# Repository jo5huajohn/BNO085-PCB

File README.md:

# BNO085 Breakout Board

Built using KiCad.

## PCB

## Schematic

## 3D Renders

Front Render

Back Render

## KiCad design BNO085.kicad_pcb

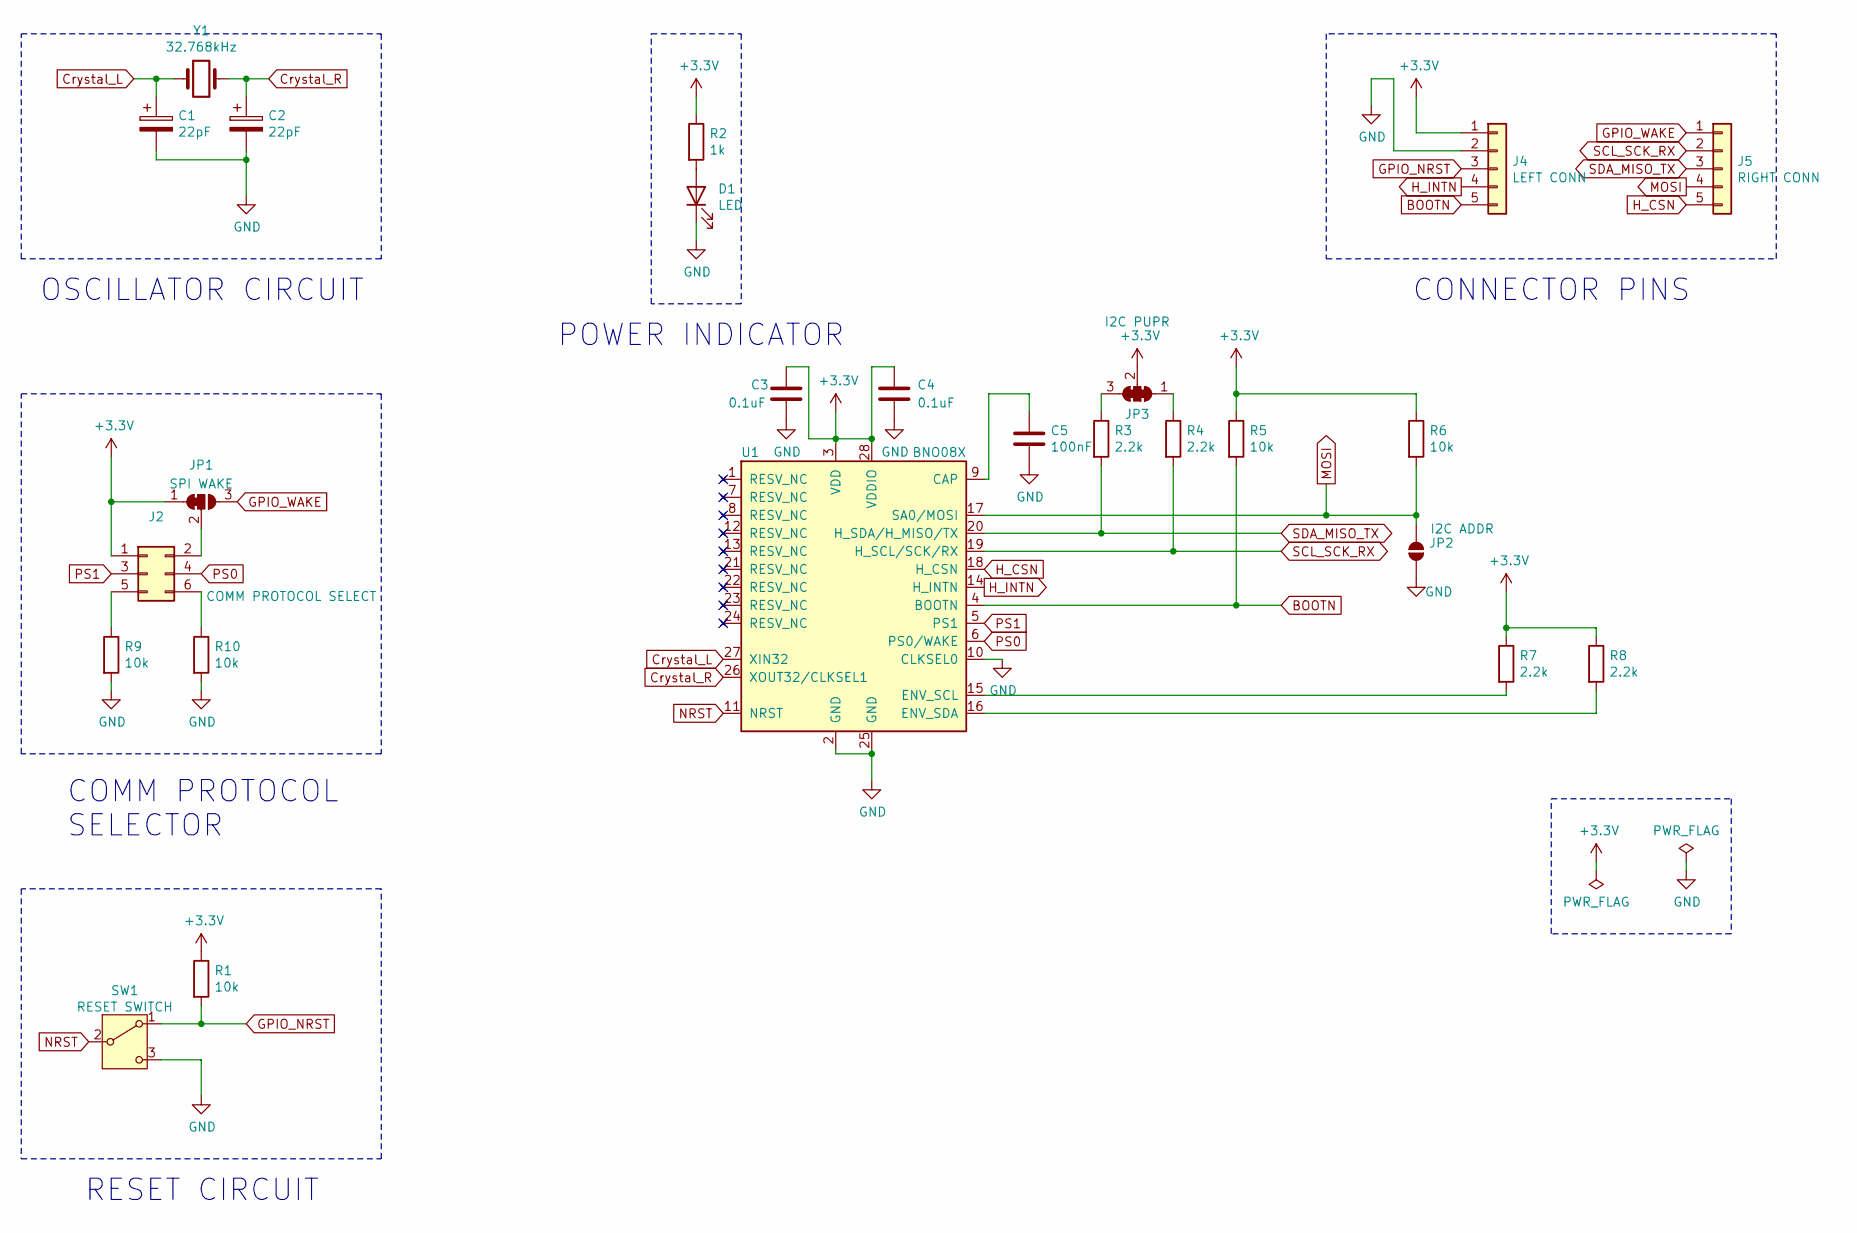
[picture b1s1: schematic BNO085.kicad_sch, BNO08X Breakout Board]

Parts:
C1, C2: 22pF; C_0603_1608Metric_Pad1.08x0.95mm_HandSolder
C3, C4: 0.1uF; C_0603_1608Metric_Pad1.08x0.95mm_HandSolder
C5: 100nF; C_0603_1608Metric_Pad1.08x0.95mm_HandSolder
D1: LED; LED_0603_1608Metric_Pad1.05x0.95mm_HandSolder
J2: COMM PROTOCOL SELECT; PinSocket_2x03_P2.54mm_Vertical
J4: LEFT CONN; PinHeader_1x05_P2.54mm_Vertical
J5: RIGHT CONN; PinHeader_1x05_P2.54mm_Vertical
JP1: SPI WAKE; SolderJumper-3_P1.3mm_Bridged12_RoundedPad1.0x1.5mm
JP2: I2C ADDR; SolderJumper-2_P1.3mm_Open_RoundedPad1.0x1.5mm
JP3: I2C PUPR; SolderJumper-3_P1.3mm_Open_RoundedPad1.0x1.5mm
R1, R5, R6, R9, R10: 10k; R_0603_1608Metric_Pad0.98x0.95mm_HandSolder
R2: 1k; R_0603_1608Metric_Pad0.98x0.95mm_HandSolder
R3, R4, R7, R8: 2.2k; R_0603_1608Metric_Pad0.98x0.95mm_HandSolder
SW1: RESET SWITCH; SW_SPST_TL3305A
U1: BNO08X; BNO08X_LGA
Y1: 32.768kHz; Crystal_SMD_3215-2Pin_3.2x1.5mm

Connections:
+3V3: C3.1, C4.1, J2.1, J4.1, JP1.1 (A), JP3.2 (C), R1.1, R2.1, R5.1, R6.1, R7.1, R8.1, U1.3 (VDD), U1.28 (VDDIO)
BOOTN: J4.5, R5.2, U1.4 (BOOTN)
Crystal_L: C1.1, U1.27 (XIN32), Y1.1
Crystal_R: C2.1, U1.26 (XOUT32/CLKSEL1), Y1.2
GND: C1.2, C2.2, C3.2, C4.2, C5.2, D1.1 (K), J4.2, JP2.2 (B), R9.2, R10.2, SW1.3 (C), U1.2 (GND), U1.10 (CLKSEL0), U1.25 (GND)
GPIO_NRST: J4.3, R1.2, SW1.1 (A)
GPIO_WAKE: J5.1, JP1.3 (B)
H_CSN: J5.5, U1.18 (H_CSN)
H_INTN: J4.4, U1.14 (H_INTN)
MOSI: J5.4, JP2.1 (A), R6.2, U1.17 (SA0/MOSI)
NRST: SW1.2 (B), U1.11 (NRST)
unnamed: C5.1, U1.9 (CAP)
unnamed: D1.2 (A), R2.2
unnamed: J2.2, JP1.2 (C)
unnamed: J2.5, R9.1
unnamed: J2.6, R10.1
unnamed: JP3.1 (A), R4.1
unnamed: JP3.3 (B), R3.1
unnamed: R7.2, U1.15 (ENV_SCL)
unnamed: R8.2, U1.16 (ENV_SDA)
PS0: J2.4, U1.6 (PS0/WAKE)
PS1: J2.3, U1.5 (PS1)
SCL_SCK_RX: J5.2, R4.2, U1.19 (H_SCL/SCK/RX)
SDA_MISO_TX: J5.3, R3.2, U1.20 (H_SDA/H_MISO/TX)

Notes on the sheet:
COMM PROTOCOL SELECTOR
OSCILLATOR CIRCUIT
CONNECTOR PINS
POWER INDICATOR
RESET CIRCUIT

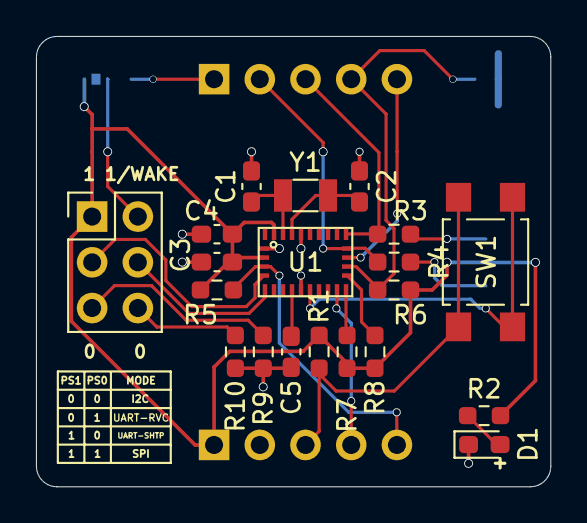
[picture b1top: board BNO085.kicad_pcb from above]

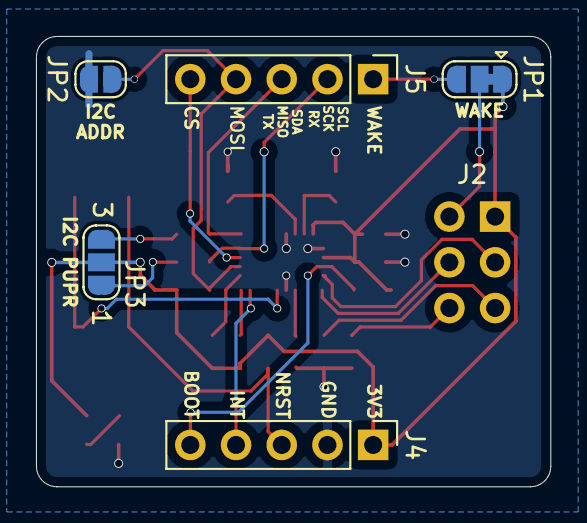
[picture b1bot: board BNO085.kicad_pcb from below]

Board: 2 copper layers, 28.6 x 25.0 mm, 25 parts (5 on the bottom side), 24 nets.

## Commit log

2026-03-02 Add BNO085 KiCad project files and diagrams
2026-03-02 Add image links to README for BNO085 board
    Updated README.md to include images with links for PCB, schematic, and 3D renders.
